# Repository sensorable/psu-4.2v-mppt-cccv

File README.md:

# MPPT 4.2v Li-Ion charger and SBC PSU
#### For use with Sensorable Open Source Camera v.1

The PSU board combines an MPPT (Multiple Point Power Tracking) solar charger, 4.2v battery IO port and a protected 4.2v output to power the main camera board.

 > This design has been **assembled with PCBA and successfully used** in temperate climate for over a year. 

![top-nocon] ![bottom-nocon]

## Specification

* **Max input working voltage:** 24V
* **Min input working voltage:** 12v
* **Max input current:** 2.5A
* **Max output current:** 6.5A
* **Max operating current:** 2A
* **Ripple:** <50mVpp nominal steady state
* **Size**: 65mm x 27mm x 15mm

#### Protection

* **Shunt Input protection:** Bipolar Zener diode, 24V working voltage, clamps to 38.9V @ 15.5A; For ESD and shunt of high-voltage surges. First line of defence. 
* **Series Input protection:** 24V working voltage 31.6V clamp, 2.5A max current. Series FETs and associated circutry will: 
Block reverse voltage. Limit current during hot-plug (for no sparks) and during surges. 
If prolonged over-voltage surge is detected charger is disabled (w/ auto-restart after surge passes) to limit power dissipated in series FETs. 
Precision over-voltage clamp (31.6V) protects switching FETs from over-voltage.  
* **Overload protection, Vbat:** None, rely on BMS. Charge current and voltage is limited by charger. 
* **Overload protection, Vout:** 4A lim; 4.5ms time constant. Retry after >500ms. Short-circuit safe.
* **Reverse polarity protection, Vin:** Safe DC voltage of +/-24V.
* **Reverse polarity protection, Vbat:** None. Charger will not attempt to charge a reversed battery but other electronics would be damaged. Batt reverse protection must be placed on BMS. 
* **Overheating protection:** Charge only when safe for Li-Ion 0C-45C, and adjust current/voltage based on temp (LT8490 feature). 
* **Electrostatic protection:** ESD/Surge protection on Input voltage, Heartbeat input, Battery voltage, Device voltage. 

## Overview

The PSU is built around [LT8490](https://www.analog.com/en/products/lt8490.html) buck-boost switching regulator battery charger with CC/CV modes and MPPT for solar input.

The purpose of the PSU is to provide a compromise between fast charging and efficient low light charging a 4P/5P/6P Li-Ion battery pack powering the main board.
The PSU incurs more losses during charging (18v -> 4.2v) to minimizes losses during discharge (4.2v direct output).
`Vout` port has an analog restart circuit for a hard reboot of the main device every 18 - 24 hrs.

![photo]

#### Heat dissipation

Switching MOSFETs, the main coil and other parts of the board require heat sinking. The board itself has more copper than the electrical design requires to help dissipate the heat, but it's not enough with passive cooling inside an enclosure. Additional heat dissipation was achieved by potting the entire assembly in a metal frame with [Electrolube ER2074](https://www.electrolube.com/products/polyurethane-epoxy-resins/er2074/resins_epoxy/) epoxy resin. It produced a sealed unit that could be exposed outside the enclosure. The best result was achieved by potting the PSU inside a standard size Al U-channel.

## Features

#### Pre-starter

Most battery protection systems require external voltage to be applied for their MOSFETs to open In/Out. On the other hand, LT8490 will not attempt to charge the battery until it measures the voltage. If the battery pack gets disconnected by its protection MOSFETs it will be restarted by a 3.3V trickle charge circuit. That voltage is enough to unlock the BMS.

![prestarter]

#### Under-voltage protection

G935 board can function with Vin > 3.4v. However, the initial draw from a 3.4v battery brings the voltage down to below that. This initiates a start-abort boot cycle that drains the battery and may even damage the board. This PSU has a special undervoltage control circuit built that disables the Vout to the device until the battery voltage reaches at least 3.7v. Once operational, the device will continue until the voltage drops to 3.20V. When off, the device is latched off until the restarter circuit triggers or the battery voltage rapidly rises (a freshly inserted battery, a freshly reset BMS). 

**Consider these scenarios:**

* battery connected, Vbat < 3.7v -> Vout = Vbat momentarily, then latches off to Vout = 0V. 
* battery connected, Vbat > 3.7v -> Vout = Vbat; operational
* battery discharging, 3.2v < Vbat < 3.7v -> Vout = Vbat; operational
* battery discharging, reboot, Vbat < 3.7v -> Vout = Vbat momentarily, then latches off to Vout = 0V. 
* battery charged to 3.7v, reboot -> Vout = Vbat; operational

![undervoltage]

#### Restarter

Given the remote nature of the PSU deployment a **hard reboot** on a schedule (approx every 27hrs) safeguards from the main board freezing for whatever reason. It is the equivalent of turning the power off for a few seconds. 

A restarter **heartbeat** wire (P3.2) can be connected to an NFC pin on G935 boards to prevent the restart. When NFC is enabled G935 sends a short burst of pulses to the restarter resetting the timer.

**Heartbeat signal requirements:** Rising edge or edges (such as sine waves from NFC) with >2V positive peaks. Must be present for >1ms.  Then, must relax for  2s < t << 27 hrs.  For example, send a 1ms NFC pulse every 5s/5min/5hour. 
Can also be operated with DC with similar timing/voltage requirements.  
Will not work with consistent output, must be pulsed.  

#### Connectors

![board-top] ![board-bottom]

#### IP68 USB-C connector

 input from a solar panel or a wall charger. This connector provides a sealed connection up to 2A per contact and remains waterproof when decoupled. Amphenol LTW part number: UC-31PFFP-QS8001. Mates with UC-20AMM-QA8A01 or similar.

![usbc] ![pushup]

**Pushup board:** the angle of the USB-C connector didn't allow mounting it directly on the PSU board, so we had to use a separate riser (push-up) board to align it with the enclosure. 

 > **We recommend using a simpler and cheaper external connector in your design.**

Field notes: 
* the connector proved to be reliable over 2 years of use with low mating cycles
* make sure the air was pushed out when inserting - it may push the male out
* using a plug is recommended if not coupled to stop fouling the contacts
* plugging in a USB-C charger won't work because the starting voltage is < 6v and the board don't have the means to negotiate a higher Vin. 

#### Other connectors

**4.2v battery contacts**: use 17AWG - 13AWG wires or D < 1.8mm to connect the battery pack. Must be soldered.

**4.2v device power**: use 22AWG - 17AWG wires or D < 1.2mm to connect the main board. Must be soldered.

[photo]: img/mppt-schematics.png
[board-top]: img/mppt-board-top.jpg
[board-bottom]: img/mppt-board-bottom.jpg
[input-filter]: img/mppt-input-filter.png
[usbc]: img/uc-31pffp-qs8001_sml.jpg
[prestarter]: img/mppt-prestarter.png
[undervoltage]: img/mppt-undervoltage.png
[pushup]: img/pushup-assembled.png
[top-nocon]: img/board-top-nocon.jpg
[bottom-nocon]: img/board-bottom-nocon.jpg

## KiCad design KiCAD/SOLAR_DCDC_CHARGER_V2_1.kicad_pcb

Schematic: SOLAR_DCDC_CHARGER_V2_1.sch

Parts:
C1, C41, C47, C55: .047uF X7R; 0402_Medium_pads; Voltage 25V; Manufacturer1PartNumber GRM155R71E473KA88D
C2, C5: .33uF X7R; 0603_Medium_Pads; Voltage 25V; Manufacturer1PartNumber CGA3E3X7R1E334K080AB
C3, C9, C12, C14, C19, C20, C29, C34, C36, C37, C38, C42, C43, C45, C54, C56, C57, C61, C64, C66, C68, C69, C70, C71, C72, C73, C80: 10uF X5R; 1206_Medium_Pads; Voltage 50; Manufacturer1PartNumber GRT31CR61H106ME01L
C4, C7, C28, C40, C46, C48, C49, C62, C67, C74, C78, C79: 1000pF X7R; 0402_Medium_pads; Voltage 50; Manufacturer1PartNumber CC0402KRX7R9BB102
C6: .033uF X7R; 0402_Medium_pads; Voltage 25V; Manufacturer1PartNumber CC0402KRX7R8BB333
C8, C16, C75, C76, C81: 8200pF X7R; 0402_Medium_pads; Voltage 50; Manufacturer1PartNumber CL05B822KB5NNNC
C10, C13, C15: DNU; 0402_Medium_pads; Voltage V; Manufacturer1PartNumber MFG1PN
C11, C50, C65: 1000pF X7R; 0603_Medium_Pads; Voltage 50; Manufacturer1PartNumber 06035C102KAT2A
C17: DNU; 0603_Medium_Pads; Voltage V; Manufacturer1PartNumber MFG1PN
C18, C25, C31, C33: 1uF; 0805_Medium_Pads; Voltage 50; Manufacturer1PartNumber UMK212BJ105KG-T
C21, C24, C32, C82, C83: .1uF X7R; 0402_Medium_pads; Voltage 25V; Manufacturer1PartNumber GRM155R61E104KA87D
C22, C23, C30, C44, C52, C53, C60: 10uF; 1206_Medium_Pads; Voltage 50; Manufacturer1PartNumber GRT31CR61H106ME01L
C26, C39: .068uF X7R; 0402_Medium_pads; Voltage 50V; Manufacturer1PartNumber GRM155R71H683KE14D
C27, C35, C58, C63, C77: .033uF X7R; 0603_Medium_Pads; Voltage 50; Manufacturer1PartNumber CL10B333KB8NNNC
C51: 47uF; 1206_Medium_Pads; Voltage 6.3V; Manufacturer1PartNumber GRM31CR60J476KE19L
C59: DNU; 0402_Medium_pads; Voltage 50; Manufacturer1PartNumber MFG1PN
D1: 1A; SOD-323; Voltage 50V; Manufacturer1PartNumber \"PMEG4010EJ,115\"
D2: ZENER; VMD2; Voltage 27V; Manufacturer1PartNumber VDZT2R27B
D3, D4, D11, D12, D13, D14, D15, D16, D17: 150mA; SOD-523F; Voltage 75V; Manufacturer1PartNumber 1N4148WT
D5: 1A; SOD-123F; Voltage 50V; Manufacturer1PartNumber US1AFA
D6: 500mA; SOD-323; Voltage 30V; Manufacturer1PartNumber BAT54WS-7-F
D7: 38.9VC 600WPk; SMB; Voltage 24VWM; Manufacturer1PartNumber SMBJ24CA
D8, D9, D10: ZENER_BiDir_3pin_SOT; SOT-23; Voltage V; Manufacturer1PartNumber MMBZ5V6ALT3G
FID1, FID4: FIDUCIAL; FIDUCIAL_.75mm; Manufacturer1PartNumber FIDUCIAL
L1: INDUCTOR; 17.5x17.5mm_FullPads_2.1mmWide; Manufacturer1PartNumber IHLP6767GZER100M51
L2: 1.2uH 7.5A 10.5mOhm; 6.3x6.3mm_Inductor; Manufacturer1PartNumber SRN6045TA-1R2Y
L4: 0 ohm; 0805_Medium_Pads; Manufacturer1PartNumber RC0805JR-070RL
P1, P2, P4, P6, P7, P8, P9, P10, P11, P12, P13, P14, P15, P16, P17, P18, P19, P20, P21, P22, P23, P27: PAD; Manufacturer1PartNumber MFG1PN
P3: Conn_Basic_3_pin; CONN_3pin_just_holes_2.5mmPITCH_.72mm-1.15mmHOLES; Manufacturer1PartNumber MFG1PN
P5: Conn_Basic_2_pin; Conn_2_3x3mm_4.7mmpitch_w_1.7mm_drill; Manufacturer1PartNumber MFG1PN
P24: CONN_2x12; Amphenol-UC-31PFFP-QS8001-USB-Connectors-USB-3.1-TYPE-C-JACK; Manufacturer1PartNumber UC-31PFFP-QS8001
P25: HUBSY_RISER_BOARD_STACK; RISER_BOARD_ACCEPTOR_CONN_RCPT_2ROW_24POS_TH_RA_1.27MM__thru; Manufacturer1PartNumber 2xM50-3530542+HubsyRiserBoardV2.1+M50-3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
P26: Conn_Basic_2_pin; ALIGNMENT_HOLES_2x_2.8mmx2.0mm_20mmPitch; Manufacturer1PartNumber MFG1PN
Q1, Q11: DUAL_N_MOS_CS_SOT353; SOT-353-5pin_2x1.25mm_.65mmPITCH; Manufacturer1PartNumber DMN32D2LDF-7
Q2, Q4: N_MOS_5-DFN; DFN5_SO8FL; Manufacturer1PartNumber NTMFS5C468NLT1G
Q3, Q6: N_MOS_5-DFN; DFN5_SO8FL; Manufacturer1PartNumber NTMFS5C442NT1G
Q5: P_MOS_SOT363; SC-70-6_POWERPAK; Manufacturer1PartNumber SIA427DJ-T1-GE3
Q7, Q12, Q13: P_MOS_SOT23; SST3; Manufacturer1PartNumber RSC002P03T316
Q8: DUAL_N_MOS_LFPAK56D; LFPAK56D-8_5.2x4.6mm_1.27mm; Manufacturer1PartNumber BUK7K52-60EX
Q9, Q10, Q14, Q15: NPN_BJT_SOT23; SOT-723_1.2x.8mm; Voltage 65V; Manufacturer1PartNumber BC846BM3T5G
R1, R67, R70: 8.06k; 0402_Medium_pads; Tolerance 1%; Manufacturer1PartNumber RC0402FR-078K06L
R2, R60, R76, R80, R85, R86, R89: 1k; 0402_Medium_pads; Tolerance 1%; Manufacturer1PartNumber RC0402FR-071KL
R3, R26: 95.3K; 0402_Medium_pads; Tolerance 1%; Manufacturer1PartNumber RC0402FR-0795K3L
R4: 6.98k; 0402_Medium_pads; Tolerance 1%; Manufacturer1PartNumber RC0402FR-076K98L
R5: 14.3k; 0402_Medium_pads; Tolerance 1%; Manufacturer1PartNumber RC0402FR-0714K3L
R6: 2.87k; 0402_Medium_pads; Tolerance 1%; Manufacturer1PartNumber RC0402FR-072K87L
R7, R55, R73: 365k; 0402_Medium_pads; Tolerance 1%; Manufacturer1PartNumber RC0402FR-07365KL
R8, R16, R17, R19, R74: 21k; 0402_Medium_pads; Tolerance 1%; Manufacturer1PartNumber RC0402FR-0721KL
R9: 1k; 0402_Medium_pads; Tolerance 1%; Manufacturer1PartNumber RC0402JR-071KL
R10: 137k; 0402_Medium_pads; Tolerance 1%; Manufacturer1PartNumber RC0402FR-07137KL
R11, R71: 49.9k; 0402_Medium_pads; Tolerance 1%; Manufacturer1PartNumber RC0402FR-0749K9L
R12: 215k; 0402_Medium_pads; Tolerance 1%; Manufacturer1PartNumber RC0402FR-07215KL
R13, R18, R30, R38, R44, R47, R49, R51, R52: 0; 0402_Medium_pads; Tolerance 1%; Manufacturer1PartNumber RC0402JR-070RL
R14: 42.2k; 0402_Medium_pads; Tolerance 1%; Manufacturer1PartNumber RC0402FR-0742K2L
R15: 71.5K; 0402_Medium_pads; Tolerance 1%; Manufacturer1PartNumber RC0402FR-0771K5L
R20, R29: 11.5k; 0402_Medium_pads; Tolerance 1%; Manufacturer1PartNumber RC0402FR-0711K5L
R21: 10k 3380K; 0603_Medium_Pads; Tolerance Tol; Manufacturer1PartNumber B57330V2103F260
R22, R23, R35, R36, R37, R39, R42, R78: 4.7; 0402_Medium_pads; Tolerance 1%; Manufacturer1PartNumber RC0402FR-074R7L
R24, R43: 4.7; 0603_Medium_Pads; Tolerance 1%; Manufacturer1PartNumber RC0603FR-074R7L
R25: 53.6k; 0402_Medium_pads; Tolerance 1%; Manufacturer1PartNumber RC0402FR-0753K6L
R27, R46, R48, R50, R56, R61, R65, R68, R69, R72, R83: 196k; 0402_Medium_pads; Tolerance 1%; Manufacturer1PartNumber RC0402FR-07196KL
R28, R45, R62: 100k; 0402_Medium_pads; Tolerance 1%; Manufacturer1PartNumber RC0402FR-07100KL
R31, R64: DNU; 0402_Medium_pads; Tolerance 1%; Manufacturer1PartNumber MFG1PN
R32, R41, R66: 0.005; 0805_Medium_Pads; Tolerance 5%; Manufacturer1PartNumber CRF0805-FZ-R005ELF
R33, R58: 32.4k; 0402_Medium_pads; Tolerance 1%; Manufacturer1PartNumber RC0402FR-0732K4L
R34: 97.6k; 0402_Medium_pads; Tolerance 1%; Manufacturer1PartNumber RC0402FR-0797K6L
R40: 0.022; 0805_Medium_Pads; Tolerance 1; Manufacturer1PartNumber ERJ-6BWFR022V
R53, R77, R82, R87, R88: 150; 0402_Medium_pads; Tolerance 1%; Manufacturer1PartNumber RC0402FR-07150RL
R54, R57, R79, R81, R84: 182k; 0402_Medium_pads; Tolerance 1%; Manufacturer1PartNumber RC0402FR-07182KL
R59: 3.01k; 0402_Medium_pads; Tolerance 1%; Manufacturer1PartNumber RC0402FR-073K01L
R63: DNU; 0603_Medium_Pads; Manufacturer1PartNumber MFG1PN
R75: 0.01; 0805_Medium_Pads; Tolerance 1; Manufacturer1PartNumber RU2012FR010CS
U1: LT8490; LT8490_QFN-64_UKJ; Manufacturer1PartNumber LT8490EUKJ#PBF
U2: 74LV4060; TSSOP-16_SOT403-1_5x4.4mm_.65mmPITCH; Manufacturer1PartNumber \"74LV4060PW,112\"
U3: LT4356; MSOP-8_3x3mm_.5mmPITCH; Manufacturer1PartNumber LT4356IMS-1#TRPBF
U4, U6: MCP65R46T-1202E/CHY; SOT23-6; Manufacturer1PartNumber MCP65R46T-1202E/CHY
U5: INA199A1DCKR; SOT-363(SC-70)-6pin_2x1.25mm_.65mmPITCH; Manufacturer1PartNumber INA199A1DCKR

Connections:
AVDD: C28.1, P11.1, R18.2, R20.2, R31.1, U1.58 (AVDD)
BG1: Q3.4, R30.2
BG2: Q4.4, R38.2
CLK_DET: C26.1, R25.1, U1.56 (CLKDET)
CSNIN: C19.1, C25.1, C27.1, C29.1, C57.1, C58.1, C64.1, C66.1, Q2.5, R35.2, R40.1
CSP: Q3.1, Q3.2, Q3.3, Q4.1, Q4.2, Q4.3, R23.2, R32.1
CSPOUT: C12.1, C14.1, C34.1, C35.1, C36.1, C43.1, C45.1, C68.1, C70.1, Q6.5, R37.2, R41.2
FBOR: P2.1, R10.1, R11.2, R12.1, U1.16 (FBOUT), U1.57 (FBOR)
GND: C1.2, C2.2, C3.2, C4.2, C5.2, C6.2, C7.2, C8.1, C9.2, C11.2, C12.2, C14.2, C16.2, C17.1, C19.2, C20.2, C21.2, C22.2, C23.2, C24.2, C25.2, C26.2, C27.2, C28.2, C29.2, C30.2, C32.1, C33.2, C34.2, C35.2, C36.2, C37.2, C38.2, C40.2, C41.2, C42.2, C43.2, C44.2, C45.2, C46.2, C47.2, C48.2, C49.2, C50.2, C52.2, C53.2, C54.2, C55.2, C56.2, C57.2, C58.2, C59.2, C60.2, C61.2, C62.2, C63.2, C64.2, C65.2, C66.2, C67.2, C68.2, C69.2, C70.2, C71.2, C72.2, C73.2, C76.1, C77.2, C78.2, C79.2, C81.2, D1.2, D7.2, D8.2, D9.2, D10.2, D15.2, D16.2, P3.3, P5.2, P25.25 (GND), P25.27 (GND), P25.33 (GND), P26.1, P26.2, Q1.2, Q10.2, Q11.2, Q15.2, R1.1, R4.1, R7.2, R8.2, R11.1, R16.2, R19.1, R21.2, R22.2, R27.1, R32.2, R34.1, R44.2, R46.1, R48.1, R52.2, R57.1, R64.1, R65.1, R68.2, R70.1, R74.1, R79.1, R81.1, R84.1, U1.21 (SYNC), U1.55 (GND), U1.59 (GND), U1.62 (GND), U1.63 (CHARGECFG2), U1.65 (EXPOSED_PAD), U2.8 (GND), U3.9 (GND), U4.2 (VSS), U5.1 (REF), U5.2 (GND), U6.2 (VSS)
HEARTBEAT: P3.2, R24.1
IMON_IN: C8.2, P14.1, R16.1, R51.2, U1.10 (IMON_IN)
IMON_OUT: C16.1, P19.1, R33.1, R34.2, R59.2, U1.17 (IMON_OUT)
INTVCC: C23.1, C30.1, P8.1, R43.2, U1.7 (INTVCC), U1.9 (MODE), U1.24 (GATEVCC)
IOR: R59.1, U1.64 (IOR)
unnamed: C1.1, R12.2, R14.1
unnamed: C2.1, R5.2, R6.1
unnamed: C6.1, R9.2
unnamed: C7.1, R9.1, U1.18 (VC)
unnamed: C10.1, R22.1, U1.12 (CSN)
unnamed: C10.2, R23.1, U1.13 (CSP)
unnamed: C13.1, R39.2, U1.45 (CSPIN)
unnamed: C13.2, R35.1, U1.44 (CSNIN)
unnamed: C15.1, R37.1, U1.42 (CSPOUT)
unnamed: C15.2, R36.1, U1.41 (CSNOUT)
unnamed: C17.2, R63.2
unnamed: C18.1, D4.1, U1.27 (BOOST2)
unnamed: C18.2, L1.1, Q4.5, Q6.1, Q6.2, Q6.3, U1.29 (SW2)
unnamed: C21.1, R20.1, R21.1, U1.3 (TEMPSENSE)
unnamed: C4.1, C22.1, D17.2, P9.1, R18.1, U1.4 (VDD), U1.14 (LDO33)
unnamed: C24.1, P10.1, U1.19 (SS)
unnamed: C31.1, D5.1, U1.33 (BOOST1)
unnamed: C31.2, D1.1, L1.2, Q2.1, Q2.2, Q2.3, Q3.5, R63.1, U1.31 (SW1)
unnamed: C32.2, R71.2, R73.2, U6.4 (IN-)
unnamed: C39.1, R76.1
unnamed: C39.2, C62.1, D16.1, Q1.3, R46.2
unnamed: C40.1, D6.1, R48.2, R76.2
unnamed: C41.1, Q1.1, Q1.4, R45.2, R89.1
unnamed: C44.1, C52.1, C53.1, C60.1, C75.1, L2.1, Q8.1, R69.2, U3.2 (OUT)
unnamed: C47.1, R58.2, R65.2, U4.3 (IN+)
unnamed: C50.1, C67.1, L4.2, R75.1, U3.5 (VCC)
unnamed: C51.1, R61.2, R62.2
unnamed: C51.2, U2.9 (CTC)
unnamed: C54.1, P20.1, Q7.1, R56.1, R82.1
unnamed: C55.1, P21.1, R26.2, R64.2, U4.4 (IN-)
unnamed: C56.1, C61.1, Q5.4, R66.1, U5.5 (IN-)
unnamed: C59.1, P13.1, R1.2, R50.2, U1.54 (VINR)
unnamed: C63.1, U3.10 (TMR)
unnamed: C74.2, P22.1, Q5.3, R53.2, R67.2
unnamed: C75.2, Q8.2, R72.2, U3.3 (GATE)
unnamed: C76.2, Q8.4, Q9.3, R72.1
unnamed: C77.1, D11.2, R55.2, R57.2, U6.3 (IN+)
unnamed: C79.1, Q11.1, R60.2, U6.1 (OUT)
unnamed: C80.2, P27.1, Q12.1, R54.1, R78.2
unnamed: C81.1, C82.2, C83.1, D15.1, Q11.3, R79.2
unnamed: C82.1, D12.1, R81.2
unnamed: C83.2, D13.1, R84.2
unnamed: D2.2, R17.1, R19.2
unnamed: D3.1, Q9.1, R74.2
unnamed: D4.2, D5.2, R43.1
unnamed: D6.2, D10.1, R24.2
unnamed: D11.1, Q13.1, R60.1, R77.1, R83.1
unnamed: D12.2, D14.1
unnamed: D14.2, R80.2
unnamed: D17.1, R88.1
unnamed: P1.1, R3.1, R4.2, R5.1, R13.2, U1.15 (FBIN)
unnamed: P6.1, U1.2 (FAULT)
unnamed: P7.1, U1.51 (STATUS)
unnamed: P12.1, R27.2, U1.22 (RT)
unnamed: P15.1, U1.36 (SRVO_IIN)
unnamed: P16.1, U1.35 (SRVO_FBIN)
unnamed: P17.1, U1.38 (SRVO_FBOUT)
unnamed: P18.1, U1.37 (SRVO_IOUT)
unnamed: P23.1, R28.2, R29.2, U2.12 (MR)
unnamed: Q1.5, R29.1
unnamed: Q8.5, Q8.8
unnamed: Q10.1, R17.2
unnamed: Q11.4, R42.1
unnamed: Q11.5, R73.1
unnamed: Q12.3, R77.2
unnamed: Q7.3, Q13.3, R53.1
unnamed: Q14.1, R86.1
unnamed: Q14.2, Q15.3
unnamed: Q14.3, R89.2
unnamed: Q15.1, R85.1
unnamed: R6.2, U1.6 (FBIW)
unnamed: R2.2, R10.2
unnamed: R13.1, U1.1 (FBIR)
unnamed: R14.2, U1.5 (FBOW)
unnamed: R25.2, U1.20 (CLKOUT)
unnamed: R26.1, U5.6 (OUT)
unnamed: R30.1, U1.23 (BG1)
unnamed: R31.2, R44.1, U1.61 (CHARGECFG1)
unnamed: R33.2, U1.50 (IOW)
unnamed: R38.1, U1.25 (BG2)
unnamed: R42.2, R78.1
unnamed: R47.1, U1.28 (TG2)
unnamed: R49.1, U1.32 (TG1)
unnamed: R51.1, U1.53 (IIR)
unnamed: R52.1, U1.40 (EXTVCC)
unnamed: R58.1, U4.5 (VREF)
unnamed: R61.1, U2.11 (RS)
unnamed: R62.1, U2.10 (RTC)
unnamed: R69.1, R70.2, U3.1 (FB)
unnamed: R71.1, U6.5 (VREF)
unnamed: R82.2, U4.1 (OUT)
unnamed: R85.2, U2.7 (Q3)
unnamed: R87.1, R88.2
RESTARTER_GATE: D13.2, R67.1, R86.2, U2.3 (Q13)
SWEN0: R68.1, U1.8 (SWEN), U1.49 (SWENO)
TG1: Q2.4, R49.2
TG2: Q6.4, R47.2
VIN_Connector: C11.1, C65.1, D7.1, L4.1, P25.26 (VBUS), P25.29 (VBUS), P25.30 (VBUS)
VIN_FILT: C3.1, C9.1, C20.1, C33.1, C69.1, C71.1, C72.1, C73.1, D2.1, L2.2, R3.2, R15.2, R39.1, R40.2, R50.1, U1.46 (VIN)
VIN_RAW_POUR: D3.2, Q8.3, Q9.2, R75.2, U3.4 (SNS)
V_BAT: C37.1, C38.1, C42.1, C46.1, C49.1, C74.1, C78.1, C80.1, D8.1, P5.1, Q7.2, Q12.2, Q13.2, R2.1, R28.1, R36.2, R41.1, R45.1, R54.2, R55.1, R56.2, R66.2, R80.1, R83.2, R87.2, U2.16 (VCC), U4.6 (VDD), U5.3 (V+), U5.4 (IN+), U6.6 (VDD)
V_BAT_DEVICE: C48.1, D9.1, P3.1, Q5.1, Q5.2, Q5.5, Q5.6, R7.1
nSHDN: C5.1, P4.1, Q10.3, R8.1, R15.1, U1.11 (nSHDN)

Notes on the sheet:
June 2017
USBC POWER INPUT
RESTARTER TIMER/COUNTER
POWER CONVERSION
BATTERY OUTPUT
POWER FILTERING
Clamp to 38.9VMax
Clamp to 31.6V
Maximum Working Input Voltage: 24 V Minimum Working Input Voltage: 12V Maximum Working Input Current: 2.5A Maximum Working Charge Current: 6.5A
Shutdown charger at >27V
12s timing
27hrs without heatbeat causes a restart
SHORT CIRCUIT PROTECTION
4A lim ; 36Hz Bandwidth / 4.5ms time constant Retry after >500ms
USBC connector For reference only, connections made through Riser Board; P25
Hubsy V2 Roman Dasovic
Alignment Hole for USBC
V Divider: Ratio: .333
Set points at 1.21V & 1.065V 3.20V - 3.64V Window
Device Undervoltage Control
Rising Edge Detector
Unlatching
Restarter period = 12s * 2^13 = 27.3hrs. Relaxation period = 12s * 2^3 = 1.6 minutes
3.3V Trickle Charge "Pre-starter"
(Charge current affected by trace resistance)

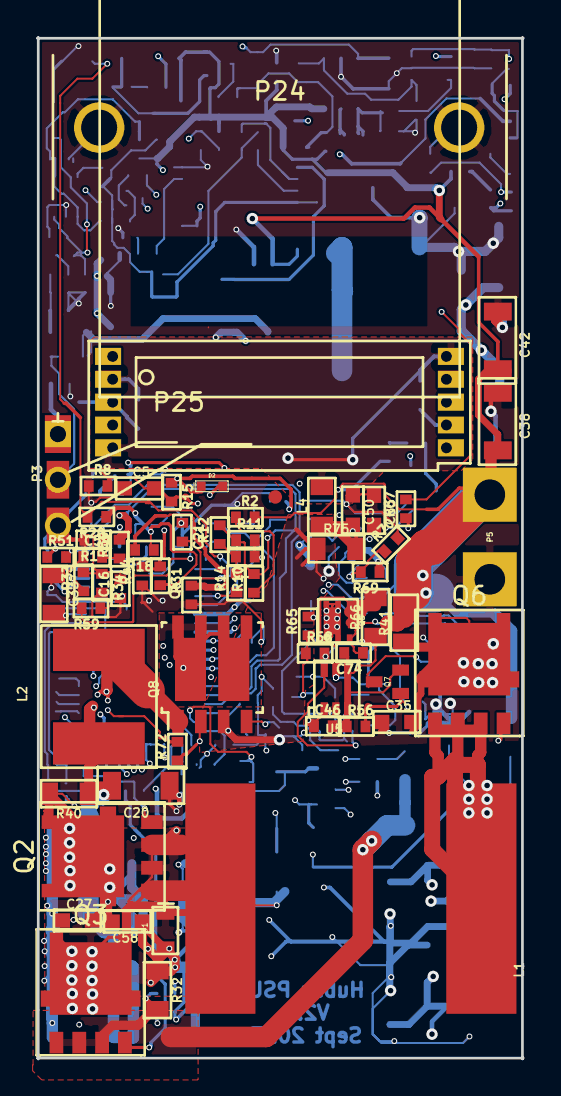
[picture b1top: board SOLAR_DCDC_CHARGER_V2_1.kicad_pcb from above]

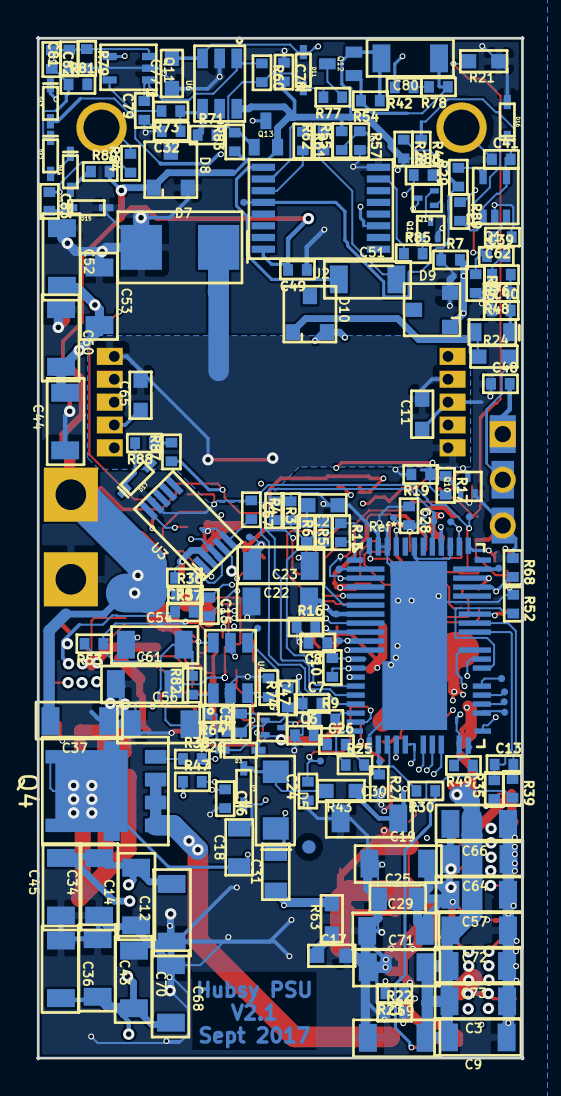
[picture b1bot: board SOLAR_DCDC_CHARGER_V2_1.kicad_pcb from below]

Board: 6 copper layers, 27.0 x 56.8 mm, 241 parts (175 on the bottom side), 117 nets.

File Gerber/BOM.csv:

Item ID,Reference,Quantity, Value, Footprint, Manufacturer1, Manufacturer1PartNumber
1,"R1,R70,R67",3,8.06k,0402_Medium_pads,Yageo,RC0402FR-078K06L
2,"R3,R26",2,95.3K,0402_Medium_pads,Yageo,RC0402FR-0795K3L
3,R4,1,6.98k,0402_Medium_pads,Yageo,RC0402FR-076K98L
4,R5,1,14.3k,0402_Medium_pads,Yageo,RC0402FR-0714K3L
5,R6,1,2.87k,0402_Medium_pads,Yageo,RC0402FR-072K87L
6,R10,1,137k,0402_Medium_pads,Yageo,RC0402FR-07137KL
7,"R11,R71",2,49.9k,0402_Medium_pads,Yageo,RC0402FR-0749K9L
8,R12,1,215k,0402_Medium_pads,Yageo,RC0402FR-07215KL
9,R14,1,42.2k,0402_Medium_pads,Yageo,RC0402FR-0742K2L
10,"R33,R58",2,32.4k,0402_Medium_pads,Yageo,RC0402FR-0732K4L
11,R34,1,97.6k,0402_Medium_pads,Yageo,RC0402FR-0797K6L
12,R40,1,0.022,0805_Medium_Pads,Panasonic,ERJ-6BWFR022V
13,"R35,R36,R39,R37,R22,R23,R78,R42",8,4.7,0402_Medium_pads,Yageo,RC0402FR-074R7L
14,"R31,C10,C15,R63,C17,C59,P3,R64,P5,C13,P20,P21,P22,P12,P13,P10,P4,P2,P11,P8,P1,P14,P23,P6,P7,P15,P9,P19,P16,P17,P18,P26,P27",0,DNU,DNU,DNU,DNU
15,"R20,R29",2,11.5k,0402_Medium_pads,Yageo,RC0402FR-0711K5L
16,R15,1,71.5K,0402_Medium_pads,Yageo,RC0402FR-0771K5L
17,R25,1,53.6k,0402_Medium_pads,Yageo,RC0402FR-0753K6L
18,"R32,R41,R66",3,0.005,0805_Medium_Pads,Bourns,CRF0805-FZ-R005ELF
19,"C33,C31,C25,C18",4,1uF,0805_Medium_Pads,Taiyo Yuden,UMK212BJ105KG-T 
20,"C23,C30,C22,C3,C9,C19,C20,C37,C60,C53,C52,C44,C34,C43,C45,C38,C42,C56,C61,C54,C66,C64,C57,C29,C73,C72,C71,C69,C36,C14,C68,C70,C12,C80",34,10uF,1206_Medium_Pads,Murata,GRT31CR61H106ME01L
21,C51,1,47uF,1206_Medium_Pads,TDK,C3216X5R0J476M160AC
22,"R62,R28,R45",3,100k,0402_Medium_pads,Yageo,RC0402FR-07100KL
23,"R2,R76,R60,R80,R89,R86,R85",7,1k,0402_Medium_pads,Yageo,RC0402FR-071KL
24,"C27,C35,C58,C63,C77",5,.033uF X7R,0603_Medium_Pads,Samsung,CL10B333KB8NNNC
25,"R50,R68,R48,R46,R61,R69,R72,R27,R56,R65,R83",11,196k,0402_Medium_pads,Yageo,RC0402FR-07196KL
26,"R44,R51,R18,R30,R38,R47,R49,R52,R13",9,0,0402_Medium_pads,Yageo,RC0402JR-070RL
27,"R8,R74,R16,R17,R19",5,21k,0402_Medium_pads,Yageo,RC0402FR-0721KL
28,R59,1,3.01k,0402_Medium_pads,Yageo,RC0402FR-073K01L
29,"C2,C5",2,.33uF X7R,0603_Medium_Pads,TDK,CGA3E3X7R1E334K080AB
30,"C26,C39",2,.068uF X7R,0402_Medium_pads,Murata,GRM155R71H683KE14D
31,"C1,C55,C41,C47",4,.047uF X7R,0402_Medium_pads,Murata,GRM155R71E473KA88D
32,"C50,C65,C11",3,1000pF X7R,0603_Medium_Pads,AVX,06035C102KAT2A
33,L1,1,INDUCTOR,17.5x17.5mm_FullPads_2.1mmWide,Vishay Dale,IHLP6767GZER100M51
34,L2,1,1.2uH 7.5A 10.5mOhm,6.3x6.3mm_Inductor,Bourns Inc,SRN6045TA-1R2Y 
35,L4,1,0 ohm,0805_Medium_Pads,Yageo,RC0805JR-070RL
36,U2,1,74LV4060,TSSOP-16_SOT403-1_5x4.4mm_.65mmPITCH,Nexperia,"74LV4060PW,112"
37,U1,1,LT8490,LT8490_QFN-64_UKJ,Linear Tech,LT8490EUKJ#PBF
38,D7,1,38.9VC 600WPk,SMB,LittelFuse,SMBJ24CA
39,U3,1,LT4356,MSOP-8_3x3mm_.5mmPITCH,Linear Tech,LT4356IMS-1#TRPBF
40,Q8,1,DUAL_N_MOS_LFPAK56D,LFPAK56D-8_5.2x4.6mm_1.27mm,Nexperia,BUK7K52-60EX
41,R75,1,0.01,0805_Medium_Pads,Samsung,RU2012FR010CS
42,"Q9,Q10,Q15,Q14",4,NPN_BJT_SOT23,SOT-723_1.2x.8mm,ON Semiconductor,BC846BM3T5G
43,D6,1,500mA,SOD-323,Diodes INC,BAT54WS-7-F
44,Q5,1,P_MOS_SOT363,SC-70-6_POWERPAK,Vishay,SIA427DJ-T1-GE3
45,D1,1,1A,SOD-323,Nexperia,"PMEG4010EJ,115"
46,D5,1,1A,SOD-123F,Fairchild/ON,US1AFA
47,"C67,C40,C62,C49,C48,C7,C28,C4,C46,C74,C78,C79",12,1000pF X7R,0402_Medium_pads,KEMET,C0402C102K5RACTU
48,"FID1,FID4",0,FIDUCIAL,FIDUCIAL_.75mm,FIDUCIAL,FIDUCIAL
49,"D3,D4,D11,D12,D14,D13,D15,D16,D17",9,150mA,SOD-523F,Fairchild/ON,1N4148WT
50,R9,1,1k,0402_Medium_pads,Yageo,RC0402JR-071KL
51,C6,1,.033uF X7R,0402_Medium_pads,Yageo,CC0402KRX7R8BB333
52,"C24,C82,C83,C32,C21",5,.1uF X7R,0402_Medium_pads,Taiyo Yuden,TMK105BJ104KV-F
53,"Q1,Q11",2,DUAL_N_MOS_CS_SOT353,SOT-353-5pin_2x1.25mm_.65mmPITCH,Diodes Inc,DMN32D2LDF-7
54,"R7,R55,R73",3,365k,0402_Medium_pads,Yageo,RC0402FR-07365KL
55,"R43,R24",2,4.7,0603_Medium_Pads,Yageo,RC0603FR-074R7L
56,"Q3,Q6",2,N_MOS_5-DFN,DFN5_SO8FL,On Semiconductor,NTMFS5C442NT1G
57,"Q2,Q4",2,N_MOS_5-DFN,DFN5_SO8FL,ON Semiconductor,NTMFS5C468NLT1G
58,U5,1,INA199A1DCKR,SOT-363(SC-70)-6pin_2x1.25mm_.65mmPITCH,Texas Instruments,INA199A1DCKR
59,"U4,U6",2,MCP65R46T-1202E/CHY,SOT23-6,Microchip,MCP65R46T-1202E/CHY
60,"C8,C16,C75,C76,C81",5,8200pF X7R,0402_Medium_pads,Samsung,CL05B822KB5NNNC
61,D2,1,ZENER,VMD2,Rohm,VDZT2R27B
62,P24,1,CONN_2x12,Amphenol-UC-31PFFP-QS8001-USB-Connectors-USB-3.1-TYPE-C-JACK,Amphenol,UC-31PFFP-QS8001
63,P25,1,HUBSY_RISER_BOARD_STACK,RISER_BOARD_ACCEPTOR_CONN_RCPT_2ROW_24POS_TH_RA_1.27MM__thru,Harwin+Hubsy,2xM50-3530542+HubsyRiserBoardV2.1+M50-3201245
64,R21,1,10k 3380K,0603_Medium_Pads,Epcos (TDK),B57330V2103F260
65,"D8,D9,D10",3,ZENER_BiDir_3pin_SOT,SOT-23,On Semiconductor,MMBZ5V6ALT3G
66,"R57,R79,R81,R54,R84",5,182k,0402_Medium_pads,Yageo,RC0402FR-07182KL
67,"R77,R82,R53,R87,R88",5,150,0402_Medium_pads,Yageo,RC0402FR-07150RL
68,"Q12,Q7,Q13",3,P_MOS_SOT23,SST3,Rohm,RSC002P03T316

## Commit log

2019-06-30 As ordered in Feb 2018.
2019-06-30 update readme.md
    added some info where max had "???"
